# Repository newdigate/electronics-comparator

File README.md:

# electronics-comparator
comparator circuit using MCP661

I have a 900 mV digital signal and I need it to be 3.3V. 

The output of AL1401 audio-to-fibreoptic is 900mV and the PLT133 Adat fibre-optic transmitter led needs 3.3V. So I thought I'd try to use an opamp as a comparator. 

When the input voltage is greater than VREF, the output will be 3V3, otherwise GND.

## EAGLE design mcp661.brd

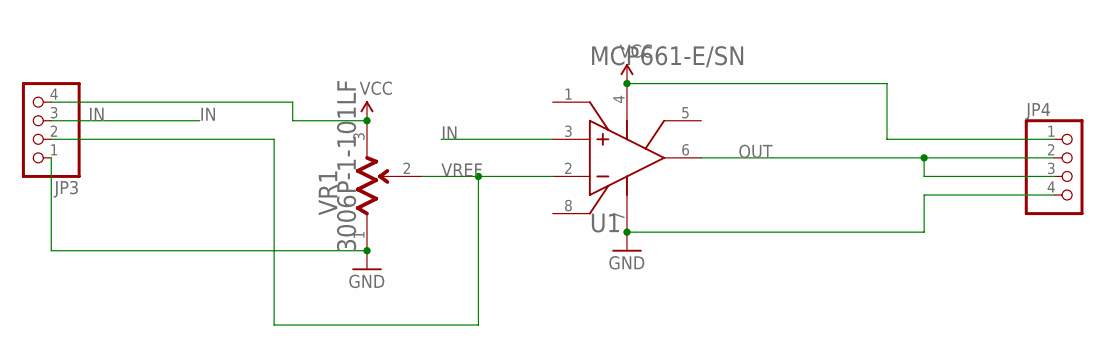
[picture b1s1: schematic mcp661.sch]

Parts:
JP3, JP4: PINHD-1X4; 1X04
U1: MICROCHIP_MCP661-E-SNMICROCHIP_MCP661-E-SN_0_2; MICROCHIP_MCP661-E-SN_2
VR1: BOURNS_3006P-1-101LFBOURNS_3006P-1-101LF_0_0; BOURNS_3006P-1-101LF_0

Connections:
GND: JP3.1, JP4.4, U1.7 (VDD), VR1.1 (CCW)
IN: JP3.3, U1.3 (VIN+)
OUT: JP4.2, JP4.3, U1.6 (VOUT)
VCC: JP3.4, JP4.1, U1.4 (VSS), VR1.3 (CW)
VREF: JP3.2, U1.2 (VIN-), VR1.2 (WIPER)

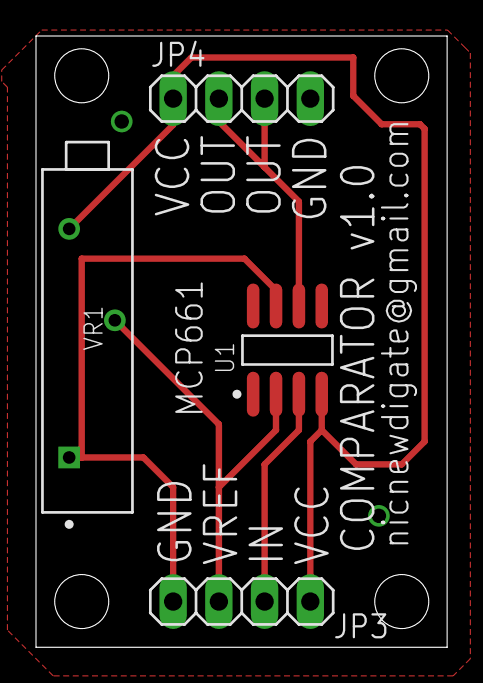
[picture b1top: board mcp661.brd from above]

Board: 2 copper layers, 22.8 x 34.0 mm, 4 parts (0 on the bottom side), 5 nets.
